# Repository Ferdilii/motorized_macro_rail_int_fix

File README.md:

# Motorized Macro Rail

Instructables Link is [here](https://www.instructables.com/DIY-Motorized-Macro-Rail/)

This is a project for a motorized macro focusing rail.  It is used with special
"stacking" software to increase the depth of field of macro images.  This
project is presented as a modification to an existing commercial rail, but could
be extended to use a custom built rail (using steel rods and linear
bearings commonly used in at-home 3D printers and CNC mahines).

## Background

Taking images of very small objects is known as [macro
photography](https://en.wikipedia.org/wiki/Macro_photography).  Using a
[specialized
lens](https://www.bhphotovideo.com/c/product/1399604-REG/venus_optics_ve2528sfe_laowa_25mm_f_2_8_2_5_5x.html),
or an [attachable
modifier](https://www.bhphotovideo.com/c/product/275182-REG/Raynox_DCR_250_DCR_250_2_5x_Super_Macro.html)
makes this type of photography possible.

Due to the [physics of photographic lenses](https://en.wikipedia.org/wiki/Depth_of_field), taking photos of very
small objects typically has a very low depth of field, where only a thin plane
of the object appears in focus, often much less than 1mm.

In general photography, it is possible to "stop down" the aperture to increase
the depth of field.  That is true in macro photography as well, but even stopping
down often does not sufficiently address the depth of field problem.

A modern solution is to take many photos where the focus point is slightly
shifted, then combine these using software.  For example, we would take these
photos:

(and 29 more)

and combine them into this "stacked" image:

The project here helps to take the captured photos in an automated and
consistent way.

Note that taking these photos requires either a specialized lens, an attachable lens
filter or an extension tube.  There are endless resources on the web on
gettings started.  Here is [one for the basics](https://digital-photography-school.com/macro-photography-for-beginners-part-1/).
Here is one for [extreme macro](https://ferdychristant.com/my-journey-into-extreme-macro-8ddef548e9f3), which is where a rail comes into play.
The amount of detail in this article is impressive and seems beyond what you'll
need to know to start experimenting, but a useful reference as you progress.

## Alternatives

### Manual Approaches

* You can use manual focus on your lens to vary the focus distance. That said,
it can be challenging to get the step size correct and consistent (especially on a
lens not designed primarily for manual focus).  The final stacked image will
thus often have "blurry" areas where there was no in-focus source image to use.
There is also the risk of moving the camera every time you touch it.  Still,
this can be a great way to start and get famiiar with the process.  This method
also does not limit you to small objects as stacking larger scenes can be useful
too.
* You can buy a manual focus rail at many different qualities and price points.
That is the starting point for this project.  The nice thing about these rails
is that they are easy to pack up for field work.  The downside is
that using them manually can feel like tedious work and you risk moving the
camera and introducing vibrations as you interact with the rail.

### Automated approaches

* You can buy commercial rails at different price points.  Here is
[one](https://cognisys-inc.com/stackshot-macro-rail-package.html) and
here is [another](https://www.wemacro.com/US/index.php/product/wemacro-rail-with-power-bank-cable-for-outside/).
Price aside, I think a downside of these solutions is the
interface.  One uses buttons and the other uses a phone app - both seem a bit
cumbersome compared to an analog stick when it comes to positioning the camera.
* [Some cameras](https://fujifilm-x.com/en-gb/learning-centre/using-focus-bracketing-and-stacking/)
have built in [focus stacking](https://en.wikipedia.org/wiki/Focus_stacking)
features while others support remote
control phone/computer [apps](https://camranger.com/camranger-2/) that add the
feature. A limitation here is that you will be limited to autofocus lenses and
[higher-magnification](https://www.bhphotovideo.com/c/product/1712870-REG/venus_optics_ve9028fe_laowa_90mm_f_2_8_2x.html) lenses usually do not offer autofocus as an option.

## Parts List

These are the parts and equipment I used.  Of course, any of them could be
swapped with alternatives with varying degrees of challenge depending on the
part:

### Parts

Prices are what I found in late 2024.  I am mostly suggesting
[Digikey](http://www.digikey.com) here because they let you purchase low part
counts.

* [Stepper motor](https://www.amazon.com/gp/product/B0B93L4H57) ($11) Any Nema 17 motor designed
for 3D printers will work well.  I'm using a lower power pancake style motor, which is still
sufficient for the job (as the leverage on a macro rail knob is very high)
* [Raspberry PI Pico](https://www.digikey.com/en/products/detail/raspberry-pi/SC0915/13624793) ($4).  You could
opt for the [unit with Wifi/Bluetooth](https://www.digikey.com/en/products/detail/raspberry-pi/SC0918/16608263)
if you want to try and trigger your camera wirelessly but note that this
enhancement will require firmware changes and could be a challenge.
* [128x128 OLED](https://www.amazon.com/dp/B0CFF435XZ) ($12).  The UI is 
designed for this resolution using a 8x16 font.  With some firmware changes, you
could go with a 128x64 and switch to an 8x8 font.  See
[src/firmware/README.md](src/firmware/README.md) for more details.
* [4 push-buttons](https://www.digikey.com/en/products/detail/schurter-inc/1301-9314-24/8536705) ($1).
* [Joystick](https://betafpv.com/products/literadio-transmitter-nano-gimbal-for-literadio-3-and-2-se?variant=39628763529350) ($6).
I'm using an RC gimbal (pitch-roll type) which gives a feeling of precise control.  You
an get these new or salvage one from an old RC radio.  Alternatively,
you can opt for a commonly-available ["PS2 stick"](https://www.amazon.com/HiLetgo-Controller-JoyStick-Breakout-Arduino/dp/B00P7QBGD2)
that will be less precise but possibly good-enough.
* [Voltage Regulator](https://www.digikey.com/en/products/detail/texas-instruments/LM7805CT-NOPB/3901929) ($2) most stepper
motors need a minimum of 12V, which is beyond what the PI Pico onboard regulator
can accept as input, thus you'll need a regulator to help it out.  I went with the famous
[LM7805](https://www.digikey.com/en/products/detail/texas-instruments/LM7805CT-NOPB/3901929) which will be powering the Pico
and OLED.  Anything between 3.3V and 5V which can deliver > 200 mA should be well
into the sufficiency range.
* [A4988 Stepper Motor Driver](https://www.amazon.com/HiLetgo-Stepstick-Stepper-Printer-Compatible/dp/B07BND65C8) ($2).
A Pico microcontroller is not designed to power a motor directly and you will need
power electronics.  The [A4988](https://www.pololu.com/file/0j450/a4988_dmos_microstepping_driver_with_translator.pdf)
gives you both the power and an easy-to-use interface which make the motor run smooth and quiet (using microstepping) and provides a number of protections (such as overcurrent protection).
* [Power connector](https://www.amazon.com/dp/B09128LHGG) ($2).
I'm going with a XT-60 connector used with RC LIPO batteries but it's really up to you.  The design will
support between 12V and around 30V but you'll want to double check the limits
of your chosen motor and voltage regulators.
* [Camera remote shutter release](https://www.digikey.com/en/products/detail/same-sky-formerly-cui-devices/SJ1-2503A/738680) ($1).  I went with
a 2.5mm jack for this but since it's the not the camera side, your options
are flexible.  Many cameras support a simple electronic shutter release.  If yours
doesn't, you can probably improvise something or go with the manual shutter
release option the firmware provides (more on that later).
* [4N25 Optocoupler](https://www.digikey.com/en/products/detail/liteon/4N25/385762) (< $1)
This is used to trigger the camera.  An [optocoupler](https://en.wikipedia.org/wiki/Opto-isolator) triggers the camera using light,
meaning that the electrical system of the camera and focus rail are fully isolated.  This electrical
isolation can bring some peace-of-mind about connecting your camera.
* [100 Ohm resistor](https://www.digikey.com/en/products/detail/vishay-dale/RLR07C1000GSB14/3141196) (<$1)
The optocoupler needs one of these.
* [470 uF capacitor](https://www.digikey.com/en/products/detail/rubycon/6-3YXJ470M6-3X11/3134408) (<$1)
The a4988 motor driver requests one of these on the motor voltage input to smooth
out voltage transisents that are common with powering motors.
* [2x 10 uF capacitor](https://www.digikey.com/en/products/detail/tdk-corporation/FK28X5R0J106MR000/2815522) (<$1) These help smooth the 5V power supply.

You will also need a rail.  I went with the [NM-200s](https://www.amazon.com/dp/B0BXKFGLF3?th=1)
which I acquired on sale for $150.  I'd say the [NM-180s](https://www.amazon.com/dp/B08BCCFQC3)
is likely as good for $130 retail.  There are also a number of cheaper options that I have no
direct experience with, such as [this one for $89](https://www.amazon.com/Adjustment-Photography-360%C2%B0Rotating-Compatibility-MS18/dp/B0C89CLJ8N).  If you go with a NM-XX0s rail as I used, you can use the provided `.STL` files directly.  For other rails
you will need to resize the adapter using the free OpenSCAD and instructions provided later
in this document.

### Equipment

* 3D printer.  This is used to create the motor-to-rail interface and
the housing for the electronics.  There are many techniques with wood working,
metalworking, [CNC](https://www.sainsmart.com/products/sainsmart-genmitsu-cnc-router-3018-pro-diy-kit),
etc, that could be alternatively used if you have the needed skills and equipment.
* Camera gear.  More on that in the process walkthrough later.  In short, just about
any camera with interchangeable lenses can be used. 

## Electronics Build

Here is the schematic.

There are around 2 dozen connections to be made here which makes most
assembly methods possible.  Here is the whole thing implemented on
a breadboard:

You could transfer the electronics to a [perf board]() and be done
with this step.  

Since I have a 3018 CNC machine, I decided to go a little farther and cut out a PCB:

Here is the board flipped over and populated with components:

If you want to use a CNC, chemical etch, or order a manufactured board,
you can find the needed files in the [`motor_rail_kicad/`](motor_rail_kicad) directory.

## Code Build

Here you have the "easy" option of uploading a precompiled `.uf2` file to your
Pico or the "flexible" option of building the binary yourself.  Both options are
free.

### Precompiled

There are many guides for how to do this, just a Google search away. Here is my
version.

* While holding down the `BOOTSEL` button, plug in the Pico via USB
* It should mount as a USB drive
* Copy the [`firmware/macro_rail_automater.uf2`](firmware/macro_rail_automater.uf2) file to the USB drive
* Unplug and replug the Pico

There are alternatives you can explore as well:

* There is a [`picotool`](https://github.com/raspberrypi/picotool) program which
allows you to load the `macro_rail_automater.uf2` file directly.  I prefer it.
* [Pin 30 on the Pico](https://www.raspberrypi.com/documentation/microcontrollers/pico-series.html#pinout-and-design-files) is named `RUN`.  If you drive it to 0V, it will reset the PICO.
If you do this while holding `BOOTSEL`, you can upload firmware which is
ergonomically easier and with less USB port wear-and-tear.  I
put a switch between `RUN` and ground (battery negative) whenever I go with a
Pico for this reason (as is done in the schematic above).

### Build firmware yourself

To start, you'll need a working development environment.  I'll point you to the
[official docs](https://datasheets.raspberrypi.com/pico/getting-started-with-pico.pdf) if you are not there yet.  I personally prefer following Appendix C "Manually configure your environment" first over the VS Code docs, then add VS Code later so I have both options available.

Once your blinking light project is working, you are nearly done.  Here
are the command line instructions (use the official Pico docs as a guide for VS Code)

* First, go into the [`src/`](src) directory.
* In Linux, type [`./bootstrap.sh`](src/bootstrap.sh).  In Windows, you'll need to follow
the steps listed in `./bootstrap.sh` which are identical to the official
docs.
* `cd build`
* `make`

At this point, you'll hopefully have your own `macro_rail_automater.uf2` file that you can load
on the your Pico.

## Macro Rail Physical Interface

The goal is to interface the stepper motor with the macro rail of your
choosing.  I ended up going with the [NM-200s](https://www.amazon.com/dp/B0BXKFGLF3)
focusing rail which I find sufficient but not amazing.  It has some flex which
leads to some shifts between photos but the stacking software compensates for this.
I *might* try a cheaper one or potentially DIY one with some steel rods and
linear bearings, if I find the time/motivation.

For the route I took, only two printed parts are needed.  One interfaces
the rail to the motor using a clamping interface:

The other printed part interfaces the motor shaft to the finger adjustment
knob:

I have included rendered `.stl` files in the [3d_models/stl](3d_models/stl)
directory that you make be able to use directly if you have a compatible rail.

If you do not have a a matching rail, you can probably make a few tweaks to the
model and have a working result.  By using the freely-available [OpenSCAD](https://openscad.org/), you can adapt
the clamp interface to various different rails by editing
[`motor_mount/focus_rail.scad`](3d_models/motor_mount/focus_rail.scad) and changing
the following parameters to match your rail:

```
RAIL_BODY_WIDTH = 37.8;
RAIL_BODY_HEIGHT = 20;
```

The numbers above (in mm) are for the [NM-200s](https://www.amazon.com/dp/B0BXKFGLF3).

The knob interface design should be adaptable to most (but not all) rail
designs.  The file to change is [`motor_mount/knob.scad`](3d_models/motor_mount/knob.scad)
with the following variables likely being relevant:

```
KNOB_DIAMETER = 15.1;
KNOB_INSET_DIAMETER = 13.2;
...
finger_cutout_diameter = 4;
finger_cutout_count = 8;
```

## Motor Current Calibration

You will need to calibrate your A4988 driver board to set the current properly
for your chosen stepper motor.  Intructions on how to calibrate are
[here](https://www.pololu.com/product/1182) with alternate instructions
[here](https://ardufocus.com/howto/a4988-motor-current-tuning/).

## Firmware Settings

If you power on the unit and press the "previous button", you are taken to
a menu that lets you chang the following settings:

* Max Velocity: The maximum motor turn speed.  Too high of a value may cause the
stepper motor to miss steps or lead to long spin down times if acceleration
is not risen to match.
* Acceletaion: The maximum motor acceleration/decelleration.  Too high of a
a value may cause the motor to miss steps or lead to rail vibrations.
* Backlash: When the motor switches direction, it will take some slack before
the main gear is engaged, this is known as backlash.  If you want a perfect
value, you can run the test mode with a caliper attached to the rail.
It's usually not critical that this number be fully tuned.
* Settle Seconds: This is how long the controller should wait between
stopping the rail and taking a photo.  The intent is to allow any
vibrations/oscillations from rail decelleration to subside.  You
can also use this value to give your camera more time to write to
its memory card.

### Steps / mm

This final menu item relates to both your motors steps/rotation and
your rails rotations/mm.  The a4988 driver is configured in the schematic
above to 16x microstep mode, meaning that 16 steps equal one step on the motor.
The formula to use is thus:

```
  motor_steps_per_rotation * 16 / mm_per_rotation
```

For my case,
I'm personally using a
[200 steps/rotation stepper motor](https://www.amazon.com/gp/product/B0B93L4H57) and a 
[1 rotation/mm rail](https://www.amazon.com/dp/B0BXKFGLF3),
thus my number will be 200 * 16 / 1 = 3200.

## Controller Case

In the folder [3d_models/controller](3d_models/controller/), there is a file named [controller.scad](3d_models/controller/controller.scad), which OpenSCAD will render like this:

This model is intended for the parts and PCB model that I'm using.  If you went
with different parts, made a differently-shaped PCB, or do not have a CNC
machine for the acrylic cover, you can either try to modify the given design or
make a custom one using whatever parts / methods work for you.

If you want to start with an STL file, you can find one at [3d_models/stl/controller.stl](3d_models/stl/controller.stl)

If you want to edit the OpenSCAD model directly, it can be found at
[3d_models/controller/controller.scad](3d_models/controller/controller.scad).
The model is parametric and has many varialbes you can change and experiement
with.  The bottom of the file allows you to turn components on and off using th the usual OpenSCAD prefixes of `*`, `!` and `//`:

```
// comment out everything but controller for the 3d print model
controller(false);
placed_pcb();
placed_gimbal(); 
cover();
// comment out everything but this to create a dxf projection
//cover_projection();
```

The `cover_projection()` can be used to create a `.dxf` export for CNC or a laser cut.
Alterrnatively, you can 3D print the cover, likely with some modifications
to allow the screen to be viewed:

An exported DXF is available at [3d_models/dxf/controller_cover.dxf](3d_models/dxf/controller_cover.dxf) if you would like to use that as your starting point.

## Process Walkthrough

This section talks about the end-to-end experience of using the rail.

### Setup

You first need to attach the stepper motor to the rail by sliding it on and
*gently* tightening the bolts (don't overdo it).  The motor can easily be
detached if you don't need it for a given session.`

Next line up the camera and target and make sure that nothing is moving.

It's good to have a light on your subject to reduce to exposure time and make
the light consistent.  Where you place the light is an artistic choice but side
lighting is a good starting point.  Flash is an option but you might need to
slow down your process to allow the flash to charge between shots.

You'll want manual everything on your camera, focus, shutter speed, aperture,
ISO and white balance.  If these parameters change in any of the photos,
it can create problems with the stacking software.

I suggest f/5.6, f/8 or f/11 for aperture.  Wider apertures will have (possibly
not perceptible) sharpness improvements due to less diffraction but you
will need to take more images to due to less depth of field.

### Find most distant point

Power on the focusing rail and use the joystick to find the farthest out point
(note you can also find the closest point first, if you prefer).

### Find closest point

Hit the 'next' button and find the closest point.

### Choose shot delay

Hit the 'next' button to choose the shot delay. My exposure settings indicate
that a photo will take 1/8th of a second to take.  You also want to think about how
long the camera will take to write the photo to the SD card (most cameras will buffer
shots in memory, but maybe not enough).  If your camera offers a setting for
["electronic shutter"](https://photographylife.com/mechanical-electronic-shutter-efcs),
I suggest turning it on as any amount of
[shutter shock](https://photographylife.com/shutter-shock) is especially
visible during macro work.

If you don't have the remote shutter working with your camera, you have
the option of choosing `0.0` here.  In that case, the rail will pause
after each photo, giving you as much time as you need to manually take
the photo.  In this mode, the "next" button is used to continue.

### Choose image count

The correct image count depends on many variables:

- How magnified the subject actually is
- How many megapixels your camera has and if you plan to pixel peep
- Your choice of aperture setting

You'll need to experiment.  If you do not know where to begin, I suggest f/8
and 0.2mm and see how it goes (or try [this chart](https://www.wemacro.com/?p=529)).

Hit the 'next' button and choose your shot count

### Take photos

Hit the `next` button to take all of the photos.  You can pause/resume the process
with the `next` button or cancel it with the `back` button.  If you find a need
to abort everything quickly or just want to start over, you can press the `reset`
button (I suggest using next/back over reset if the motor is spinning).

When all photos are taken, you have the option of repeating the process in the
reverse direction with the 'next' button or starting over with the 'back' button.

### Load onto computer and run software

I suggest Helicon focus for reasonably priced, turn key software with a free trial
period.  The software is for mac or windows but I am running it in Linux with Wine
and it runs fine.

If you want a free/open source solution, check out the [focus stack](https://github.com/PetteriAimonen/focus-stack)
project.  The main downside of going this route is that the excellent
post-stack retouching features of Helicon are not present, but many people
are able to use the software to produce excellent images regardless:

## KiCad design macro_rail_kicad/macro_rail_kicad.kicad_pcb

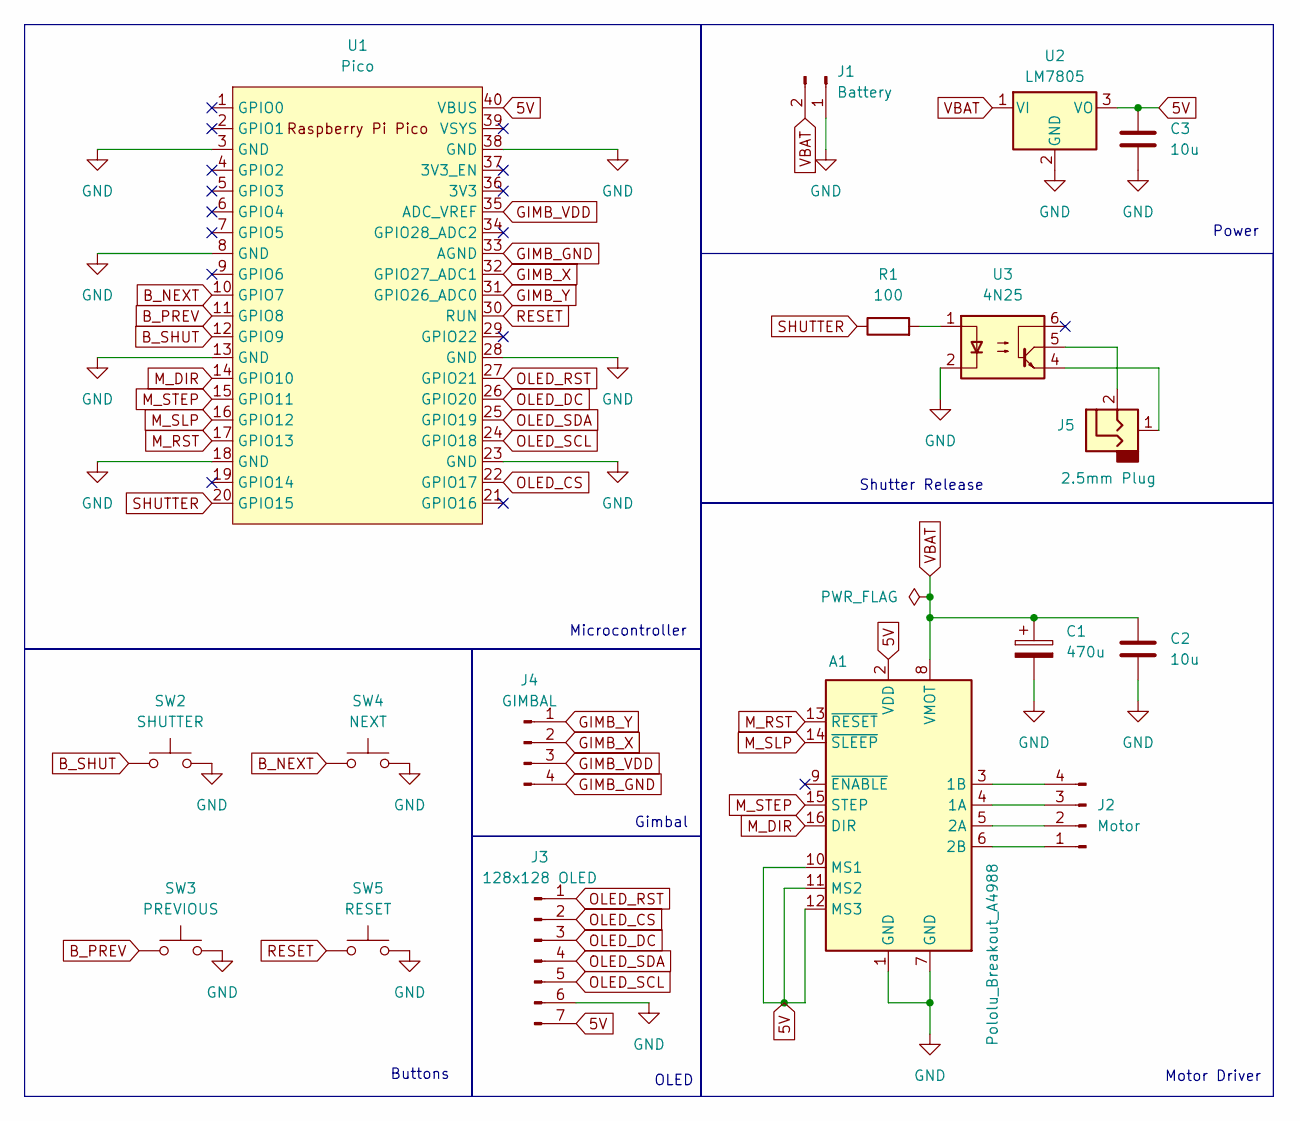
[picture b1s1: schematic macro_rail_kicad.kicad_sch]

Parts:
A1: Pololu_Breakout_A4988; Pololu_Breakout-16_15.2x20.3mm
C1: 470u; CP_Radial_D6.3mm_P2.50mm
C2, C3: 10u; C_Disc_D3.8mm_W2.6mm_P2.50mm
J1: Battery; PinHeader_1x02_P2.54mm_Vertical
J2: Motor; PinHeader_1x04_P2.54mm_Vertical
J3: 128x128 OLED; OLED_128_128_1.5in
J4: GIMBAL; PinHeader_1x04_P2.54mm_Vertical
J5: 2.5mm Plug; PinHeader_1x02_P2.54mm_Vertical
R1: 100; R_Axial_DIN0411_L9.9mm_D3.6mm_P12.70mm_Horizontal
SW2: SHUTTER; SW_PUSH_6mm_H4.3mm
SW3: PREVIOUS; SW_PUSH_6mm_H4.3mm
SW4: NEXT; SW_PUSH_6mm_H4.3mm
SW5: RESET; SW_PUSH_6mm_H4.3mm
U1: Pico; RPi_Pico_SMD_TH
U2: LM7805; TO-220-3_Vertical
U3: 4N25; DIP-6_W7.62mm

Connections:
5V: A1.2 (VDD), A1.10 (MS1), A1.11 (MS2), A1.12 (MS3), C3.1, J3.7, U1.40 (VBUS), U2.3 (VO)
B_NEXT: SW4.1, U1.10 (GPIO7)
B_PREV: SW3.1, U1.11 (GPIO8)
B_SHUT: SW2.1, U1.12 (GPIO9)
GIMB_GND: J4.4, U1.33 (AGND)
GIMB_VDD: J4.3, U1.35 (ADC_VREF)
GIMB_X: J4.2, U1.32 (GPIO27_ADC1)
GIMB_Y: J4.1, U1.31 (GPIO26_ADC0)
GND: A1.1 (GND), A1.7 (GND), C1.2, C2.2, C3.2, J1.1, J3.6, SW2.2, SW3.2, SW4.2, SW5.2, U1.3 (GND), U1.8 (GND), U1.13 (GND), U1.18 (GND), U1.23 (GND), U1.28 (GND), U1.38 (GND), U2.2 (GND), U3.2
M_DIR: A1.16 (DIR), U1.14 (GPIO10)
M_RST: A1.13 (~RESET), U1.17 (GPIO13)
M_SLP: A1.14 (~SLEEP), U1.16 (GPIO12)
M_STEP: A1.15 (STEP), U1.15 (GPIO11)
unnamed: A1.4 (1A), J2.3
unnamed: A1.3 (1B), J2.4
unnamed: A1.5 (2A), J2.2
unnamed: A1.6 (2B), J2.1
unnamed: J5.1, U3.4
unnamed: J5.2, U3.5
unnamed: R1.2, U3.1
OLED_CS: J3.2, U1.22 (GPIO17)
OLED_DC: J3.3, U1.26 (GPIO20)
OLED_RST: J3.1, U1.27 (GPIO21)
OLED_SCL: J3.5, U1.24 (GPIO18)
OLED_SDA: J3.4, U1.25 (GPIO19)
RESET: SW5.1, U1.30 (RUN)
SHUTTER: R1.1, U1.20 (GPIO15)
VBAT: A1.8 (VMOT), C1.1, C2.1, J1.2, U2.1 (VI)

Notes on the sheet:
Buttons
Shutter Release
Power
Gimbal
Motor Driver
Microcontroller
OLED

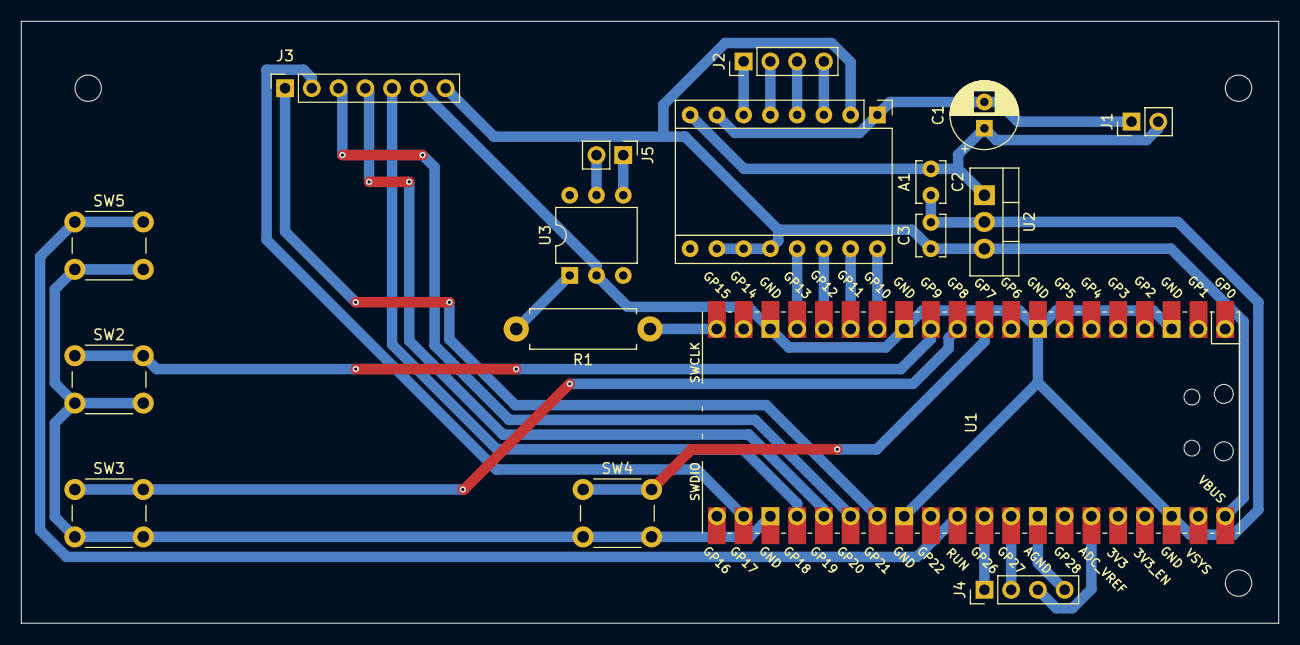
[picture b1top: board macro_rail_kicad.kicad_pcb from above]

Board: 2 copper layers, 119.4 x 57.2 mm, 17 parts (0 on the bottom side), 28 nets.

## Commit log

2024-10-19 Initial usecase analysis doc.
2024-10-19 add formatting hints
2024-10-27 added basic rail body
2024-10-28 added foot design
2024-10-28 added feet and moved foot to a separate file
2024-10-28 Moved focus_rail and foot to separate files and translated them to put 0,0,0 at a convienient spot.
2024-10-28 Added knob model
2024-10-28 made knob finger part parametric for later cutout
2024-10-28 Positioned knob
2024-10-28 Added motor base.
2024-10-28 Added motor mounting holes
2024-10-28 finished motor vitamin
2024-10-28 Placed motor in main design
2024-11-01 Added some base code for running the display.
2024-11-13 Changed blinking main.c to "hello world" on a 128x128 OLED.
2024-11-17 Setup basic framework for state changes.
2024-11-17 Made fatal errors cleaner to create.
2024-11-17 Added back main led blink which was somehow lost.
2024-11-17 Added more hookup details to comment. Some minor bug fixes.
2024-11-18 Added gimbal and debounce sources.
2024-11-18 Moved over motor driver sources.
2024-11-18 Added per-frame gimbal updates.
2024-11-18 Drafted implementation for end point selection.
2024-11-18 Fixed logic bug in new jog code.
2024-11-18 Added a delay before sleep is enabled.
2024-11-18 Restructured rending.
2024-11-18 Added backlash meter.
2024-11-18 Updated end_point_select to support start and end points.
2024-11-18 Added support for button presses.
2024-11-19 Changing the motor driver logic to allow for evenly-space high and low cycle times.
    It's unclear if this is necessary, but every example I can find uses evenly-spaced times.
    This does make the code a bit more complex to understand and may have introduced bugs.
    Some additional validation with the driver emulator and oscilliscope is needed.
2024-11-19 Worked on backlash ui
2024-11-19 Fixed even step time logic.
    The only was didn't work as visible on an oscilliscope. The new way
    scales motor pos by 2 and uses the parity to set a high-low.
    This seems to mostly owrk but I now see some step mismatches that
    are minor but perhaps worth looking into more.
2024-11-19 fixed backlash scaling calculation
2024-11-19 Removed micro side step, zero after end point
    - microstep didn't work well due to backlash
    - zero afrer end point is a logical time to do it and saves a button
2024-11-19 Added framework for shutter delay UI.
    Created render_common.h for common UI functions (render_title, currently).
2024-11-19 Drafted shutter speed UI entry.
2024-11-19 refactored end_point_select update and added some support for previous button
2024-11-19 Added back and forward UIs
2024-11-19 Display bug fixes from previous change.
2024-11-19 Only allow delay if start pos is <>1mm
2024-11-20 Added untested draft of shot count.
2024-11-20 Fixed minor rendering and cal bugs from last commit.
2024-11-20 Added run logic. NOT TESTED.
2024-11-20 Fixed some issues on post code review.
2024-11-21 Fixed various minor bugs.
    Fixed shutter GPIO number.
    Stop elasped time at end of shoot.
    Fix reverrse calculation (casting was needed).
2024-11-21 Added motor seek calculation for better overall time calculation.
    The math is a bit tricky so it might need some revs.
2024-11-22 Added flange
2024-11-22 Added motor bracket.
2024-11-23 Fixed the non-centered knob issue.
2024-11-23 Started kicad schematic.
2024-11-27 Added menu logic (untested)
2024-11-27 Added parameter change UI and max_velocity user of said UI (not tested).
2024-11-28 Added saved_setting module.
2024-11-28 Incorporate saved settings into max velocity parmeter ui.
2024-11-28 Implemented test mode and settings commit for max_velocity.
2024-11-28 Added ability to change acceleration.
2024-11-28 Get settle time from settings instead of const.
2024-11-28 Added backlash parameter change.
2024-11-29 Added settle seconds configuration.
2024-11-29 Added steps per mm configruation UI.
2024-11-29 Organized schematic.
2024-11-29 Added optocoupler and cleaned up ERC errors.
2024-11-30 Fxied some footpring issues annd imported initial netlist into pcb.
2024-11-30 Finished draft of PCB
2024-11-30 Added mounting holes. Fixed DRC violations.
2024-12-02 Started on README
2024-12-02 Schematic tidying
2024-12-02 More README work
2024-12-03 Added build docs
2024-12-04 Spell fix
2024-12-04 README links updates. Removed power switch (amps too low)
2024-12-04 Removed obsolete test dir
2024-12-04 Added maual mode to shutter delay.
2024-12-04 More README updates.
2024-12-05 Added options for more fonts and other controllers.
2024-12-05 Added some untested support for 128x64 OLEDs
2024-12-05 Added stl models and README updates.
2024-12-09 Readme updates
2024-12-09 Fixed sign issue that broke the jogging code (during a refactor)
2024-12-09 Fixed polarity of manual shutter delay.
2024-12-09 Tweaked estimated time.
    Something is still off with the calculations, but it's an improvement.
    I need to look deeping into this later.
2024-12-09 Reducued menu item visibility count to 4.
    To avoid wiping out title underline.
2024-12-09 Hopefully fixed test bug for max veliocity
2024-12-09 Put in some baic UDB logging which is off by default.
    Using it to look further into saved settings not saving.
2024-12-09 Disable CPU1 during flash write.
    Looking at an old project I see this was done and remember debugging
    the issue in the past. It makes sence that writing flash needs
    a very quiet environment to work properly.
    With this, I likely don't need the debug stuff I added earlier, but
    I'll keep in it place until I see eveything working as expected.
2024-12-09 motor_control_stop -> motor_control_stop_loop
    Noticed this while reviewing the codee diff. emoved the old functin sig
    to avoid future confusing over its ambiguous name.
2024-12-11 Fixed logging bugs. Fixed saved_settings checksum bug.
2024-12-12 Fixed bugs in acceleration ui
2024-12-12 Fixed bugs in backlash ui
2024-12-12 Fixed bugs in settle_seconds ui
2024-12-12 Fixed bugs in steps_per_mm ui
2024-12-13 fixed backlash test movemnt bug
2024-12-13 fixed settle seconds test bugs
2024-12-13 Possibly corrected steps_per_mm calculations in shot_count.
    It was getting late so I decided not to test until tomorrow.
2024-12-13 Added a4988 motor calibration.
2024-12-13 Readme update
2024-12-14 Fixed shot suggest calculation
2024-12-14 Updated firmware project name
2024-12-15 Added pcb exports.
2024-12-15 Changed firmware to use microstepping.
    The sleep need to be delayed to avoid motor snap on wake issues which
    are especially problematic during shooting. Right now
    I'm using a 10 second delay, but it should be made smarter.
2024-12-15 Updated schmatic and pcb for microstepping
2024-12-15 Updated gcode for microstep routing
2024-12-15 Up sleep time to 30 seconds
2024-12-15 removed a4988 calibration because it was not working
2024-12-15 Updated parts list.
2024-12-15 Added prebuilt firmware.
2024-12-15 Added details on the rail and motor calibration.
2024-12-15 Updates schematic and pcb images.
2024-12-15 Reorganized 3d models
2024-12-15 Started on controller, added gimbal vitamin.
2024-12-17 Updated GPIO asssignments to match schematic.
    GPIOs were moved around during the PBC layout to make the layout easier.
2024-12-18 Started PCB model for controller
2024-12-18 Added Pico to PCB
2024-12-18 Added VREG
2024-12-18 Added optocoupler
2024-12-18 Added gimbal header
2024-12-18 Added pin headers
2024-12-18 Added caps and a4988.
2024-12-18 Added more details on taking photos
2024-12-18 Added images for assembled pcb and cut pcb.
2024-12-18 Added oled.
2024-12-19 Started shaping controller.
2024-12-19 Controller base now wraps around components.
2024-12-19 tweaking case dimensions
2024-12-19 tweaking case fillet
2024-12-20 Added mounting posts.
2024-12-20 added open_view parameter
2024-12-20 Added PCB mounting posts.
2024-12-20 Thinned controller walls
2024-12-20 Switched top plate bolts to M2.
    The 2.5mm plug can not handle thick walls.
2024-12-20 Added gimbal mounting posts
2024-12-20 added motor port
2024-12-20 added remote trigger portw
2024-12-20 Added cover and cover mount holes
2024-12-20 boot port
2024-12-20 added a4988 port
2024-12-20 added gimbal port
2024-12-20 usb port
2024-12-20 added xt-60 port
2024-12-20 Added exports for controller stl and cover dxf
2024-12-20 Added cambam model and gcode for cover.
2024-12-20 added controller png
2024-12-21 Added docs on the controller casing.
2024-12-22 raied motor port by 1.5mm
2024-12-23 Increased spindle speed.
    If I recall correctly, my CNC needs 10k for full speed.
2024-12-23 Added another spindle speed change
2024-12-23 Changed floats to doubles.
    It turns out that floats do not have suffifient precision to span beyond 10.4 mm or so.
    The result is that the moo can not find it's stopping point and the system appears
    to hang and do nothing. Changing to double will give us plenty of range
    for the future.
2024-12-23 Updated firmware to include flat to double fix.
2024-12-24 More readme refinement.
2024-12-26 Readme tweaks.
2024-12-31 Added stacked images
2024-12-31 Added remaining photos.
2025-01-11 Converted OpenSCAD models to be stand-alone
2025-01-11 Added settings image
2025-01-11 added more stacjed image examples
2025-01-11 Added A4988 image
2025-01-11 fixed image path
2025-01-13 Added youtube link and placeholder for instructables link.
2025-01-13 updated instructables link
2025-08-02 Updated shutter puse delay to work with Fuji XT-5
2025-08-02 updated commit hash for firmware
2026-03-13 Added remaining gerber export files so they can be sent to a fab.
2026-05-22 Use 64-bit arithmetic for new position calculation and no breaks
2026-05-22 Add GitHub Actions workflow for firmware build
2026-05-22 Update GitHub Actions to use latest action versions
2026-05-22 Change path for UF2 file upload to include subdirectories
